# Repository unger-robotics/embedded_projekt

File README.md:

# Selection-Panel

Browser-Dashboard ↔ WebSocket(JSON) ↔ Bridge(Python) ↔ Serial(USB) ↔ ESP32 (One-Hot Selection)

## Übersicht

Ein 10-Kanal Selection-Panel mit Hardware-Buttons, LED-Feedback und Web-Interface. Nur ein Kanal kann gleichzeitig aktiv sein (One-Hot).

| Komponente        | Technologie                           | Pfad              |
|-------------------|---------------------------------------|-------------------|
| **Firmware**      | ESP32-S3, PlatformIO, Arduino         | `firmware/`       |
| **Bridge**        | Python 3.10+, aiohttp, async          | `apps/bridge/`    |
| **Dashboard**     | React 18, TypeScript, Tailwind        | `apps/dashboard/` |
| **Hardware**      | KiCad 8, CD4021/HC595 Schieberegister | `hardware/kicad/` |
| **Dokumentation** | Markdown (SSOT), LaTeX                | `doc/`            |

## Projektstruktur

```
├── firmware/           ESP32-S3 Firmware (PlatformIO)
│   ├── src/app/        Applikationsschicht
│   ├── src/logic/      Geschäftslogik (hardware-unabhängig)
│   ├── src/drivers/    Chip-Treiber (CD4021, HC595)
│   └── src/protocol/   Serial-Protokoll (COBS/CRC)
├── apps/
│   ├── bridge/         Python WebSocket ↔ Serial Bridge
│   └── dashboard/      React SPA (Vite)
├── hardware/kicad/     Schaltplan + PCB
├── doc/
│   ├── md/             Markdown-Dokumentation (SSOT)
│   └── latex/          LaTeX/PDF-Ausgabe
└── scripts/            Deployment- und Utility-Skripte
```

## Quick Start

### Firmware flashen
```bash
cd firmware
pio run -t upload && pio device monitor
```

### Dashboard + Bridge lokal starten
```bash
# Terminal 1: Dashboard Dev-Server
cd apps/dashboard && npm ci && npm run dev

# Terminal 2: Bridge (verbindet mit ESP32)
cd apps/bridge
python -m venv .venv && source .venv/bin/activate
pip install -r requirements.txt
python bridge.py --port auto --http 8081
```

Dashboard öffnen: http://localhost:5173 (Dev) oder http://rover.local:8081/ (via Bridge)

## Dokumentation

| Thema                 | Pfad                                                |
|-----------------------|-----------------------------------------------------|
| **Claude Code Guide** | `CLAUDE.md`                                         |
| **Protokoll (SSOT)**  | `apps/bridge/docs/PROTOCOL.md`                      |
| **Build/Deploy/Run**  | `apps/bridge/docs/WORKFLOW.md`                      |
| **Smoke Test (E2E)**  | `apps/bridge/docs/SMOKE_TEST.md`                    |
| **Firmware Details**  | `firmware/CLAUDE.md`, `firmware/docs/`              |
| **Apps Details**      | `apps/CLAUDE.md`                                    |
| **Hardware (KiCad)**  | `hardware/kicad/selection-panel-prototyp/README.md` |

## Deployment (Pi)

Siehe `CLAUDE.md` für den vollständigen Deploy-Workflow (Mac → Pi) und systemd-Konfiguration.

```bash
# Kurzfassung: Dashboard bauen und zum Pi synchronisieren
cd apps/dashboard && npm run build && cd -
./scripts/deploy_pi.sh
```

Auf dem Pi: `sudo systemctl restart embedded-bridge.service`

## Lizenz

Siehe `LICENSE`.

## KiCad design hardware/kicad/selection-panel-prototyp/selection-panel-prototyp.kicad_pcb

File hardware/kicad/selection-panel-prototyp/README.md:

# Selection Panel Prototyp – KiCad 8 Projekt

## Projektinhalt

```
selection-panel-prototyp/
├── selection-panel-prototyp.kicad_pro   ← Projekt öffnen
├── selection-panel-prototyp.kicad_sch   ← Schaltplan (leer, zum Befüllen)
├── selection-panel-prototyp.kicad_pcb   ← PCB (leer, Netze vordefiniert)
└── selection-panel-prototyp.net         ← Original-Netzliste (Referenz)
```

## Workflow in KiCad 8

### 1. Projekt öffnen

```
Datei → Projekt öffnen → selection-panel-prototyp.kicad_pro
```

### 2. Symbole hinzufügen

KiCad 8 unterstützt keinen Netzlisten-Import mehr. Die Bauteile müssen manuell platziert werden:

1. **Schematic Editor** öffnen (Doppelklick auf `.kicad_sch`)
2. `A` drücken → Symbol suchen und platzieren

| Bauteil | Suchbegriff | Bibliothek |
|---------|-------------|------------|
| 74HC595 | `74HC595` | 74xx |
| CD4021 | `4021` | 4xxx |
| LED | `LED` | Device |
| Widerstand | `R` | Device |
| Kondensator | `C` | Device |
| Taster | `SW_Push` | Switch |
| ESP32 | `Conn_01x14` | Connector (als Platzhalter) |

### 3. Verbindungen zeichnen

Drähte ziehen mit `W`, oder Labels nutzen (`L`):

| Label | Von | Nach |
|-------|-----|------|
| LED_DATA | U1 Pin 1 (D0) | U2 Pin 14 (SER) |
| LED_CLOCK | U1 Pin 2 (D1) | U2/U3 Pin 11 (SRCLK) |
| LED_LATCH | U1 Pin 3 (D2) | U2/U3 Pin 12 (RCLK) |
| LED_CASCADE | U2 Pin 9 (QH') | U3 Pin 14 (SER) |
| BTN_DATA | U4 Pin 3 (Q8) | U1 Pin 4 (D3) |
| BTN_CLOCK | U1 Pin 5 (D4) | U4/U5 Pin 10 (CLK) |
| BTN_LOAD | U1 Pin 6 (D5) | U4/U5 Pin 9 (P/S) |
| BTN_CASCADE | U5 Pin 3 (Q8) | U4 Pin 11 (SER) |

### 3. Annotation prüfen

```
Werkzeuge → Schaltplansymbole annotieren → Annotate
```

### 4. ERC ausführen

```
Prüfen → Electrical Rules Checker → Run ERC
```

### 5. PCB aktualisieren

```
Werkzeuge → Update PCB from Schematic (F8)
```

Die Footprints erscheinen gestapelt. Dann:

1. Bauteile platzieren (M = verschieben, R = rotieren)
2. Leiterbahnen routen mit X
3. GND-Fläche hinzufügen

## Kritische Verbindungen

Diese Pins müssen fest verdrahtet werden:

| IC | Pin | Ziel | Begründung |
|----|-----|------|------------|
| U2, U3 | 10 (SRCLR) | VCC | Reset deaktiviert |
| U2, U3 | 13 (OE) | GND | Ausgänge aktiv |
| U5 | 11 (SER) | VCC | CMOS darf nicht floaten |

## Bauteilliste

| Ref | Wert | Footprint |
|-----|------|-----------|
| U1 | ESP32-S3-XIAO | Seeed:XIAO-ESP32S3 |
| U2, U3 | 74HC595 | Package_DIP:DIP-16_W7.62mm |
| U4, U5 | CD4021BE | Package_DIP:DIP-16_W7.62mm |
| D1–D10 | LED | LED_THT:LED_D5.0mm |
| R1–R10 | 330Ω | Resistor_THT:R_Axial_DIN0207 |
| R11–R20 | 10kΩ | Resistor_THT:R_Axial_DIN0207 |
| C1–C4 | 100nF | Capacitor_THT:C_Disc_D5.0mm |
| SW1–SW10 | Taster | Button_Switch_THT:SW_PUSH_6mm |

---

*KiCad 8.0 | Dezember 2025*

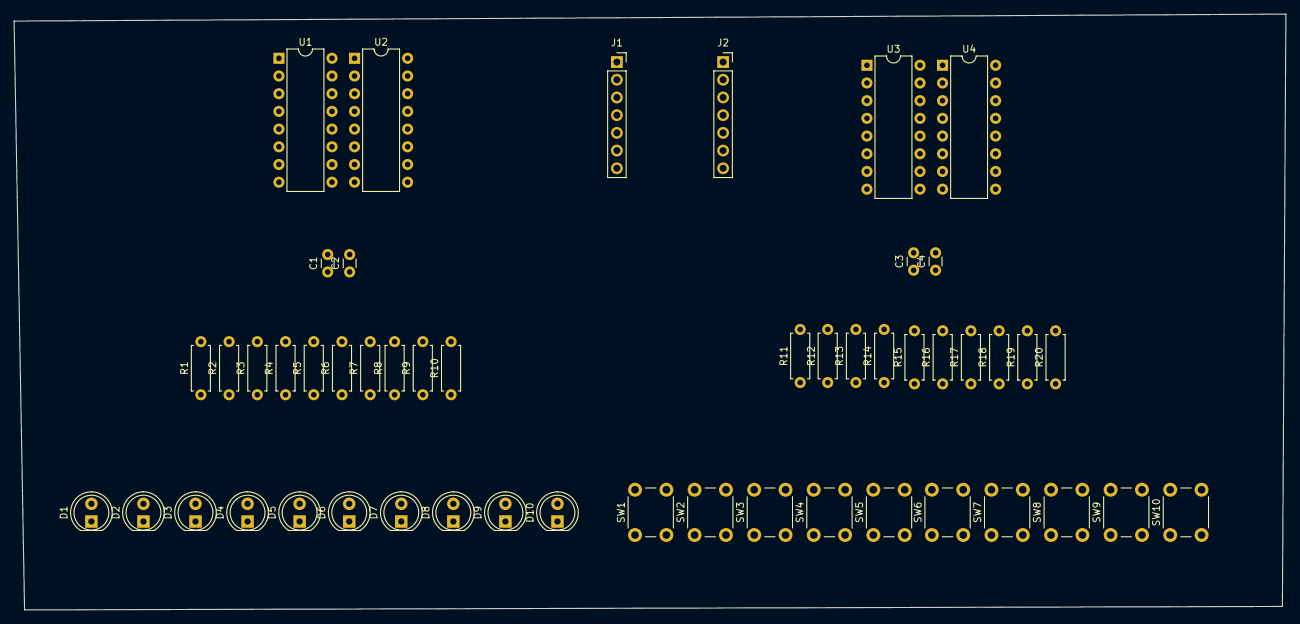
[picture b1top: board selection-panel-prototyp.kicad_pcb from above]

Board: 2 copper layers, 182.5 x 85.5 mm, 50 parts (0 on the bottom side), 40 nets, no tracks yet.

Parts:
C1, C2, C3, C4: 100n; C_Disc_D3.0mm_W1.6mm_P2.50mm
D1, D2, D3, D4, D5, D6, D7, D8, D9, D10: LED; LED_D5.0mm
J1, J2: ESP32-S3-XIAO; PinSocket_1x07_P2.54mm_Vertical
R1, R2, R3, R4, R5, R6, R7, R8, R9, R10: 330; R_Axial_DIN0207_L6.3mm_D2.5mm_P7.62mm_Horizontal
R11, R12, R13, R14, R15, R16, R17, R18, R19, R20: 10k; R_Axial_DIN0207_L6.3mm_D2.5mm_P7.62mm_Horizontal
SW1, SW2, SW3, SW4, SW5, SW6, SW7, SW8, SW9, SW10: SW_Push; SW_PUSH_6mm
U1, U2: 74HC595; DIP-16_W7.62mm
U3, U4: 4021; DIP-16_W7.62mm

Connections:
3V3: C1.2, C2.2, C3.2, C4.1, J2.3, R11.1, R12.1, R13.1, R14.1, R15.1, R16.1, R17.1, R18.1, R19.1, R20.1, U1.10 (~SRCLR), U1.16 (VCC), U2.10 (~SRCLR), U2.16 (VCC), U3.16 (VDD), U4.11 (DS), U4.16 (VDD)
/BTN_CLK: J1.5, U3.10 (CP), U4.10 (CP)
/BTN_DATA: J1.4, U3.3 (Q7)
/BTN_LOAD: J1.6, U3.9 (PL), U4.9 (PL)
/LED_CLK: J1.2, U1.11 (SRCLK), U2.11 (SRCLK)
/LED_DATA: J1.1, U1.14 (SER)
/LED_LATCH: J1.3, U1.12 (RCLK), U2.12 (RCLK)
GND: C1.1, C2.1, C3.1, C4.2, D1.1 (K), D2.1 (K), D3.1 (K), D4.1 (K), D5.1 (K), D6.1 (K), D7.1 (K), D8.1 (K), D9.1 (K), D10.1 (K), J2.2, SW1.2, SW2.2, SW3.2, SW4.2, SW5.2, SW6.2, SW7.2, SW8.2, SW9.2, SW10.2, U1.8 (GND), U1.13 (~OE), U2.8 (GND), U2.13 (~OE), U3.8 (VSS), U4.8 (VSS)
unnamed: D1.2 (A), R1.2
unnamed: D2.2 (A), R2.2
unnamed: D3.2 (A), R3.2
unnamed: D4.2 (A), R4.2
unnamed: D5.2 (A), R5.2
unnamed: D6.2 (A), R6.2
unnamed: D7.2 (A), R7.2
unnamed: D8.2 (A), R8.2
unnamed: D9.2 (A), R9.2
unnamed: D10.2 (A), R10.2
unnamed: R1.1, U1.15 (QA)
unnamed: R2.1, U1.1 (QB)
unnamed: R3.1, U1.2 (QC)
unnamed: R4.1, U1.3 (QD)
unnamed: R5.1, U1.4 (QE)
unnamed: R6.1, U1.5 (QF)
unnamed: R7.1, U1.6 (QG)
unnamed: U1.9 (QH'), U2.14 (SER)
unnamed: R8.1, U1.7 (QH)
unnamed: R9.1, U2.15 (QA)
unnamed: R10.1, U2.1 (QB)
unnamed: R17.2, SW7.1, U3.7 (D0)
unnamed: R16.2, SW6.1, U3.6 (D1)
unnamed: R15.2, SW5.1, U3.5 (D2)
unnamed: R14.2, SW4.1, U3.4 (D3)
unnamed: R12.2, SW2.1, U3.13 (D4)
unnamed: R13.2, SW3.1, U3.14 (D5)
unnamed: R18.2, SW8.1, U3.15 (D6)
unnamed: R11.2, SW1.1, U3.1 (D7)
unnamed: U3.11 (DS), U4.3 (Q7)
unnamed: R20.2, SW10.1, U4.13 (D4)
unnamed: R19.2, SW9.1, U4.1 (D7)

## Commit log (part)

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2026-01-31 docs: add CLAUDE.md, update README, CHANGELOG, .gitignore
2026-01-31 chore: remove large video files from repo, update .gitignore
